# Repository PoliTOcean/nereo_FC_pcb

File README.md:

# nereo_FC_pcb

Flight controller di Nereo (STM32F4, 2 layer).
Firmware: [nereo_FC_firmware](https://github.com/PoliTOcean/nereo_FC_firmware)

| Top | Bottom |
|---|---|
|  |  |

> I file di produzione (gerber, BOM, PDF dello schema) si scaricano dalla scheda **Actions** → ultimo run → **pcb-outputs**.

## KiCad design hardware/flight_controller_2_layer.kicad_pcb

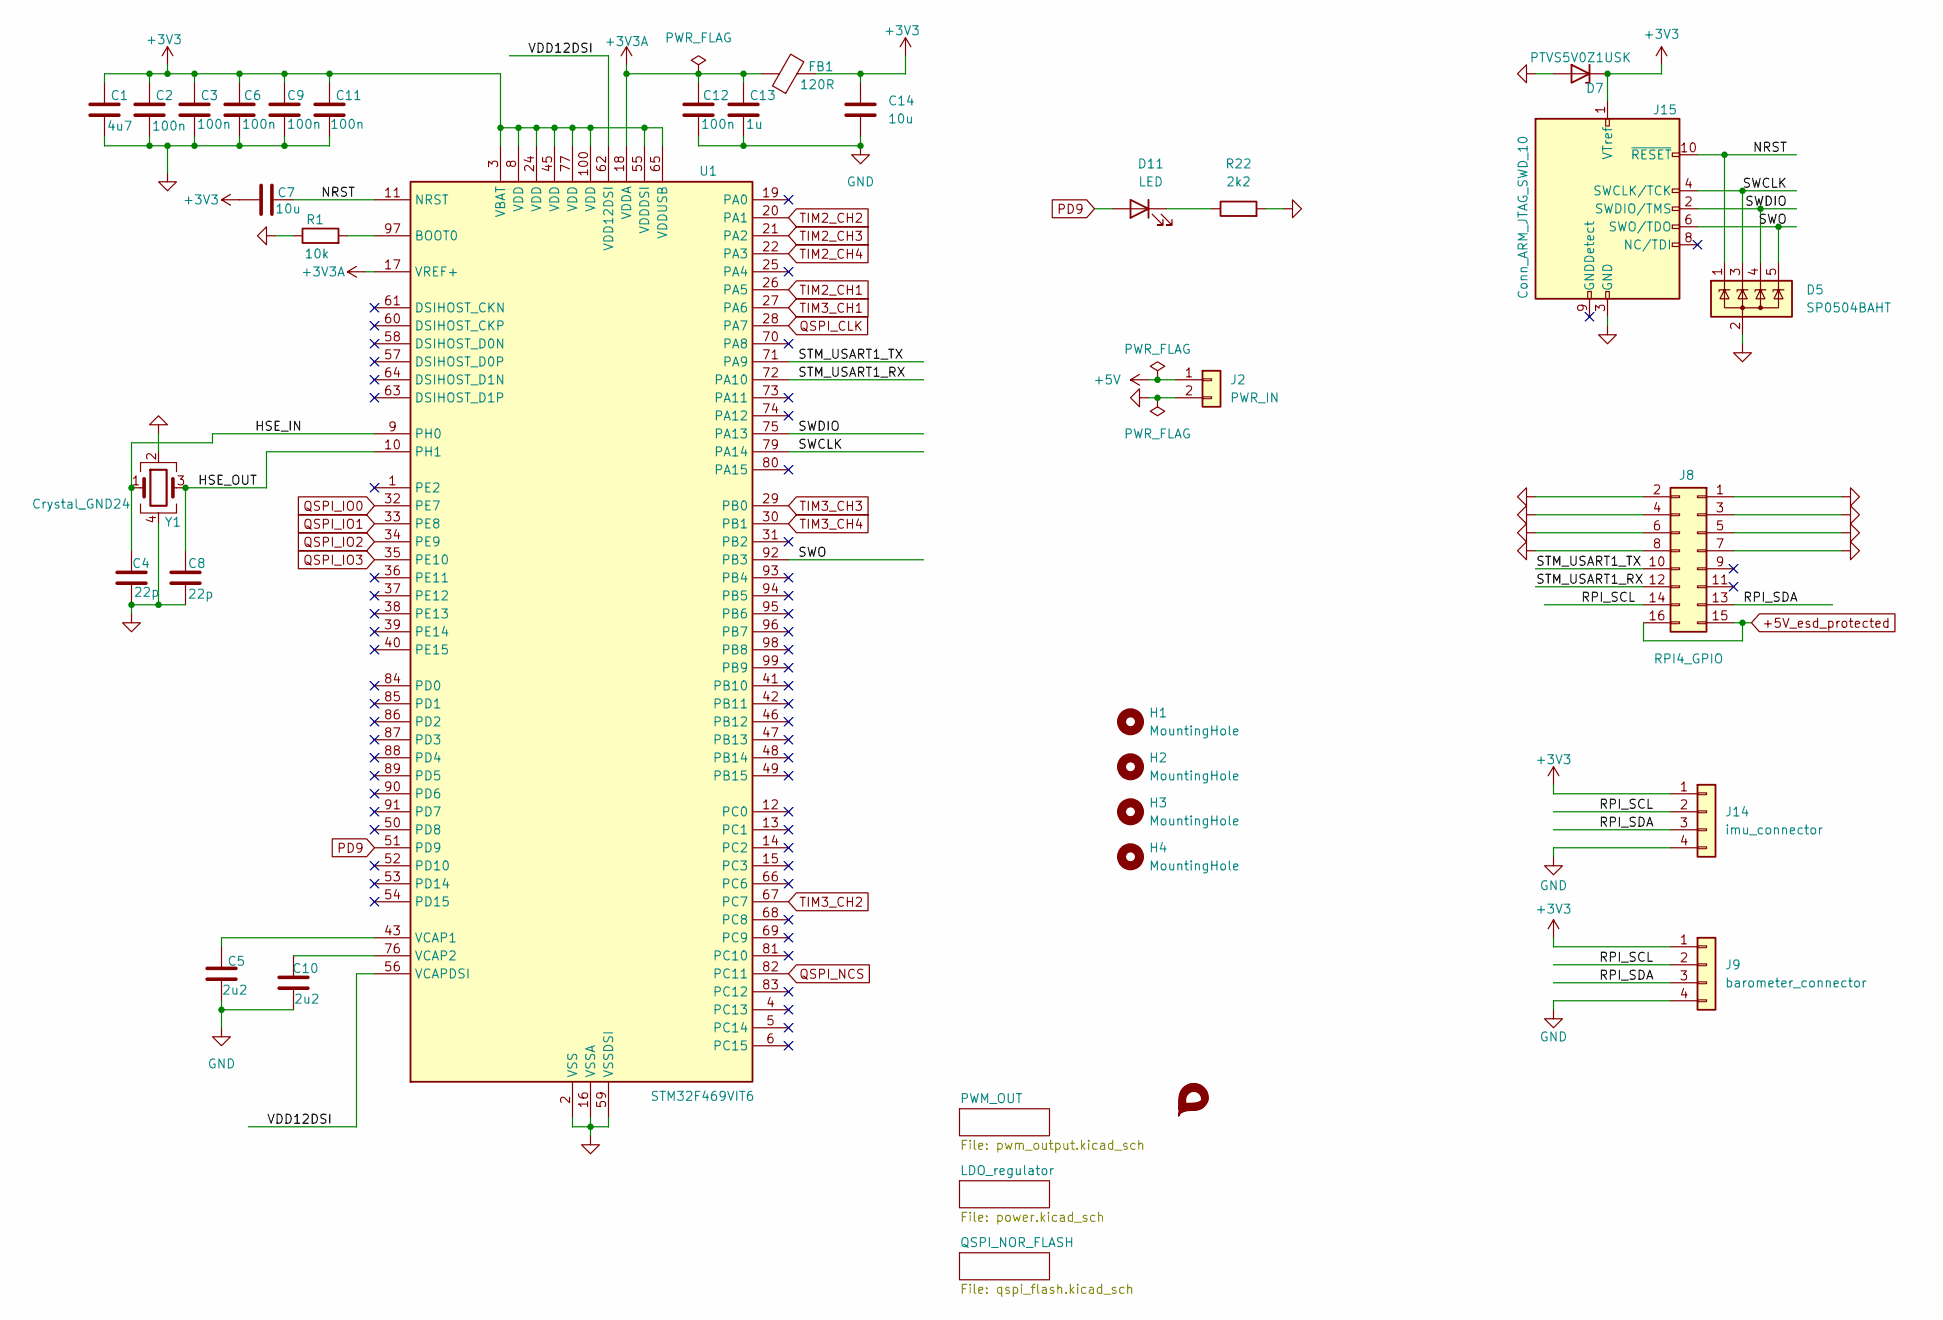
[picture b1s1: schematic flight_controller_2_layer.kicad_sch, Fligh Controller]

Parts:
C1: 4u7; C_0603_1608Metric
C2, C3, C6, C9, C11, C12: 100n; C_0603_1608Metric
C4, C8: 22p; C_0603_1608Metric
C5, C10: 2u2; C_0603_1608Metric
C7, C14: 10u; C_0603_1608Metric
C13: 1u; C_0603_1608Metric
D5: SP0504BAHT; SOT-23-5
D7: PTVS5V0Z1USK; Nexperia_DSN1608-2_1.6x0.8mm
D11: LED; LED_0603_1608Metric
FB1: 120R; L_0603_1608Metric
G1: LOGO; Logo PoliTOcean
H1, H2, H3, H4: MountingHole; MountingHole_2.7mm_M2.5
J2: PWR_IN; JST_VH_B2P-VH_1x02_P3.96mm_Vertical
J8: RPI4_GPIO; IDC-Header_2x08_P2.54mm_Vertical
J9: barometer_connector; JST_XH_B4B-XH-A_1x04_P2.50mm_Vertical
J14: imu_connector; JST_XH_B4B-XH-A_1x04_P2.50mm_Vertical
J15: Conn_ARM_JTAG_SWD_10; PinHeader_2x05_P1.27mm_Vertical_SMD
R1: 10k; R_0603_1608Metric
R22: 2k2; R_0603_1608Metric
U1: STM32F469VIT6; LQFP-100_14x14mm_P0.5mm
Y1: Crystal_GND24; Crystal_SMD_Abracon_ABM3B-4Pin_5.0x3.2mm

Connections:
+3V3: C1.1, C2.1, C3.1, C6.1, C7.1, C9.1, C11.1, C14.1, D7.1 (K), FB1.2, J9.1, J14.1, J15.1 (VTref), U1.3 (VBAT), U1.8 (VDD), U1.24 (VDD), U1.45 (VDD), U1.55 (VDDDSI), U1.65 (VDDUSB), U1.77 (VDD), U1.100 (VDD); also elsewhere on the board
+3V3A: C12.1, C13.1, FB1.1, U1.17 (VREF+), U1.18 (VDDA)
+5V: J2.1; also elsewhere on the board
+5V_esd_protected: J8.15, J8.16; also elsewhere on the board
/HSE_IN: C4.1, U1.9 (PH0), Y1.1
/HSE_OUT: C8.1, U1.10 (PH1), Y1.3
/NRST: C7.2, D5.1 (K), J15.10 (~RESET), U1.11 (NRST)
/RPI_SCL: J8.14, J9.2, J14.2
/RPI_SDA: J8.13, J9.3, J14.3
/STM_USART1_RX: J8.12, U1.72 (PA10)
/STM_USART1_TX: J8.10, U1.71 (PA9)
/SWCLK: D5.3 (K), J15.4 (SWCLK/TCK), U1.79 (PA14)
/SWDIO: D5.4 (K), J15.2 (SWDIO/TMS), U1.75 (PA13)
/SWO: D5.5 (K), J15.6 (SWO/TDO), U1.92 (PB3)
/VDD12DSI: U1.56 (VCAPDSI), U1.62 (VDD12DSI)
GND: C1.2, C2.2, C3.2, C4.2, C5.2, C6.2, C8.2, C9.2, C10.2, C11.2, C12.2, C13.2, C14.2, D5.2 (A), D7.2 (A), J2.2, J8.1, J8.2, J8.3, J8.4, J8.5, J8.6, J8.7, J8.8, J9.4, J14.4, J15.3 (GND), J15.5 (GND), R1.1, R22.2, U1.2 (VSS), U1.7 (VSS), U1.16 (VSSA), U1.23 (VSS), U1.44 (VSS), U1.59 (VSSDSI), U1.78 (VSS), Y1.2, Y1.4; also elsewhere on the board
unnamed: D11.1 (K), R22.1
unnamed: R1.2, U1.97 (BOOT0)
unnamed: C5.1, U1.43 (VCAP1)
unnamed: C10.1, U1.76 (VCAP2)
PD9: D11.2 (A), U1.51 (PD9)
QSPI_CLK: U1.28 (PA7); also elsewhere on the board
QSPI_IO0: U1.32 (PE7); also elsewhere on the board
QSPI_IO1: U1.33 (PE8); also elsewhere on the board
QSPI_IO2: U1.34 (PE9); also elsewhere on the board
QSPI_IO3: U1.35 (PE10); also elsewhere on the board
QSPI_NCS: U1.82 (PC11); also elsewhere on the board
TIM2_CH1: U1.26 (PA5); also elsewhere on the board
TIM2_CH2: U1.20 (PA1); also elsewhere on the board
TIM2_CH3: U1.21 (PA2); also elsewhere on the board
TIM2_CH4: U1.22 (PA3); also elsewhere on the board
TIM3_CH1: U1.27 (PA6); also elsewhere on the board
TIM3_CH2: U1.67 (PC7); also elsewhere on the board
TIM3_CH3: U1.29 (PB0); also elsewhere on the board
TIM3_CH4: U1.30 (PB1); also elsewhere on the board

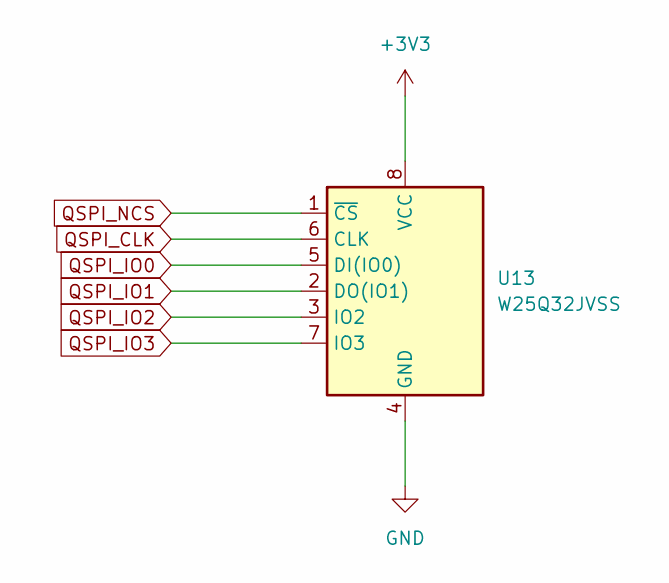
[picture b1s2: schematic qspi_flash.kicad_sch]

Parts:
U13: W25Q32JVSS; SOIC-8_5.23x5.23mm_P1.27mm

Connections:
+3V3: U13.8 (VCC); also elsewhere on the board
GND: U13.4 (GND); also elsewhere on the board
QSPI_CLK: U13.6 (CLK); also elsewhere on the board
QSPI_IO0: U13.5 (DI(IO0)); also elsewhere on the board
QSPI_IO1: U13.2 (DO(IO1)); also elsewhere on the board
QSPI_IO2: U13.3 (IO2); also elsewhere on the board
QSPI_IO3: U13.7 (IO3); also elsewhere on the board
QSPI_NCS: U13.1 (~CS); also elsewhere on the board

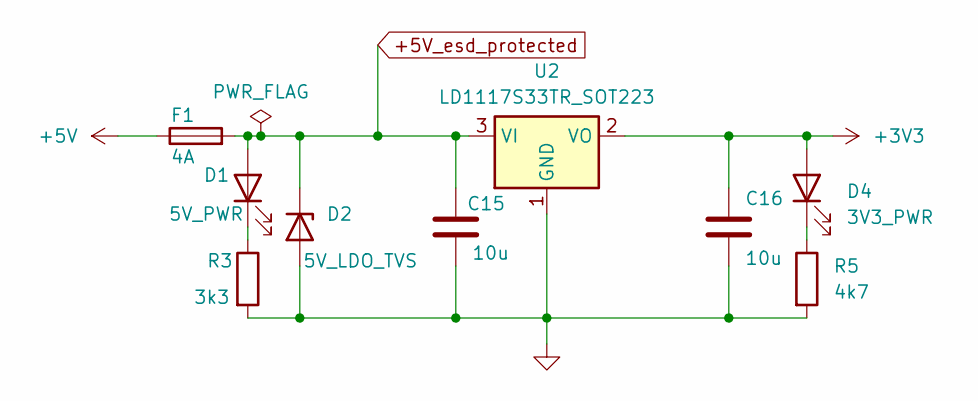
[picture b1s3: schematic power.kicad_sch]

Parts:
C15, C16: 10u; C_0603_1608Metric
D1: 5V_PWR; LED_0603_1608Metric
D2: 5V_LDO_TVS; Nexperia_DSN1608-2_1.6x0.8mm
D4: 3V3_PWR; LED_0603_1608Metric
F1: 4A; Fuseholder_Clip-5x20mm_Littelfuse_111_Lateral_P18.80x5.00mm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
R3: 3k3; R_0603_1608Metric
R5: 4k7; R_0603_1608Metric
U2: LD1117S33TR_SOT223; SOT-223-3_TabPin2

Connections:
+3V3: C16.1, D4.2 (A), U2.2 (VO); also elsewhere on the board
+5V: F1.1; also elsewhere on the board
+5V_esd_protected: C15.1, D1.2 (A), D2.1 (K), F1.2, U2.3 (VI); also elsewhere on the board
GND: C15.2, C16.2, D2.2 (A), R3.2, R5.2, U2.1 (GND); also elsewhere on the board
unnamed: D1.1 (K), R3.1
unnamed: D4.1 (K), R5.1

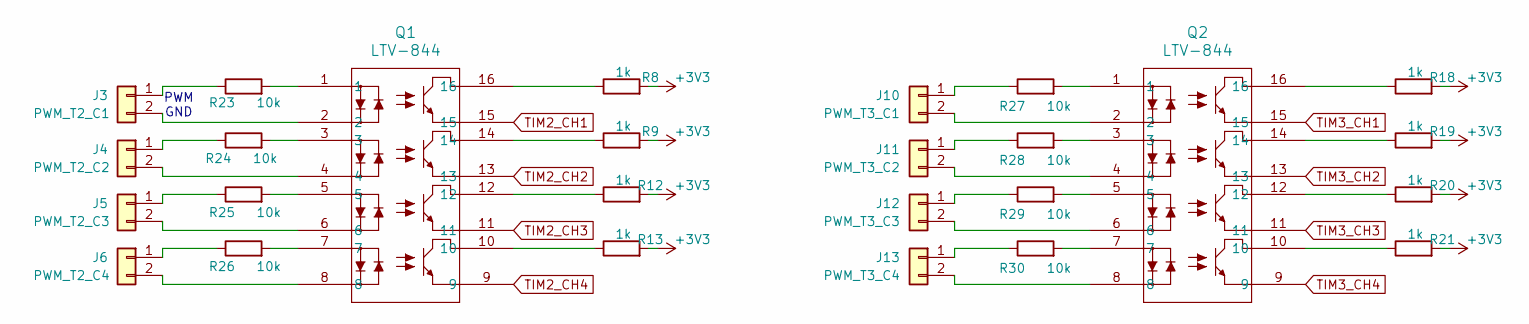
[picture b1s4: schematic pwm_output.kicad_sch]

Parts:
J3: PWM_T2_C1; JST_XH_B2B-XH-A_1x02_P2.50mm_Vertical
J4: PWM_T2_C2; JST_XH_B2B-XH-A_1x02_P2.50mm_Vertical
J5: PWM_T2_C3; JST_XH_B2B-XH-A_1x02_P2.50mm_Vertical
J6: PWM_T2_C4; JST_XH_B2B-XH-A_1x02_P2.50mm_Vertical
J10: PWM_T3_C1; JST_XH_B2B-XH-A_1x02_P2.50mm_Vertical
J11: PWM_T3_C2; JST_XH_B2B-XH-A_1x02_P2.50mm_Vertical
J12: PWM_T3_C3; JST_XH_B2B-XH-A_1x02_P2.50mm_Vertical
J13: PWM_T3_C4; JST_XH_B2B-XH-A_1x02_P2.50mm_Vertical
Q1, Q2: LTV-844; LTV-844_LTO
R8, R9, R12, R13, R18, R19, R20, R21: 1k; R_0603_1608Metric
R23, R24, R25, R26, R27, R28, R29, R30: 10k; R_0603_1608Metric

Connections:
+3V3: R8.2, R9.2, R12.2, R13.2, R18.2, R19.2, R20.2, R21.2; also elsewhere on the board
unnamed: J3.1, R23.1
unnamed: J3.2, Q1.2
unnamed: J4.1, R24.1
unnamed: J4.2, Q1.4
unnamed: J5.1, R25.1
unnamed: J5.2, Q1.6
unnamed: J6.1, R26.1
unnamed: J6.2, Q1.8
unnamed: J10.1, R27.1
unnamed: J10.2, Q2.2
unnamed: J11.1, R28.1
unnamed: J11.2, Q2.4
unnamed: J12.1, R29.1
unnamed: J12.2, Q2.6
unnamed: J13.1, R30.1
unnamed: J13.2, Q2.8
unnamed: Q1.1, R23.2
unnamed: Q1.3, R24.2
unnamed: Q1.5, R25.2
unnamed: Q1.7, R26.2
unnamed: Q1.10, R13.1
unnamed: Q1.12, R12.1
unnamed: Q1.14, R9.1
unnamed: Q1.16, R8.1
unnamed: Q2.1, R27.2
unnamed: Q2.3, R28.2
unnamed: Q2.5, R29.2
unnamed: Q2.7, R30.2
unnamed: Q2.10, R21.1
unnamed: Q2.12, R20.1
unnamed: Q2.14, R19.1
unnamed: Q2.16, R18.1
TIM2_CH1: Q1.15; also elsewhere on the board
TIM2_CH2: Q1.13; also elsewhere on the board
TIM2_CH3: Q1.11; also elsewhere on the board
TIM2_CH4: Q1.9; also elsewhere on the board
TIM3_CH1: Q2.15; also elsewhere on the board
TIM3_CH2: Q2.13; also elsewhere on the board
TIM3_CH3: Q2.11; also elsewhere on the board
TIM3_CH4: Q2.9; also elsewhere on the board

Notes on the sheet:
PWM GND

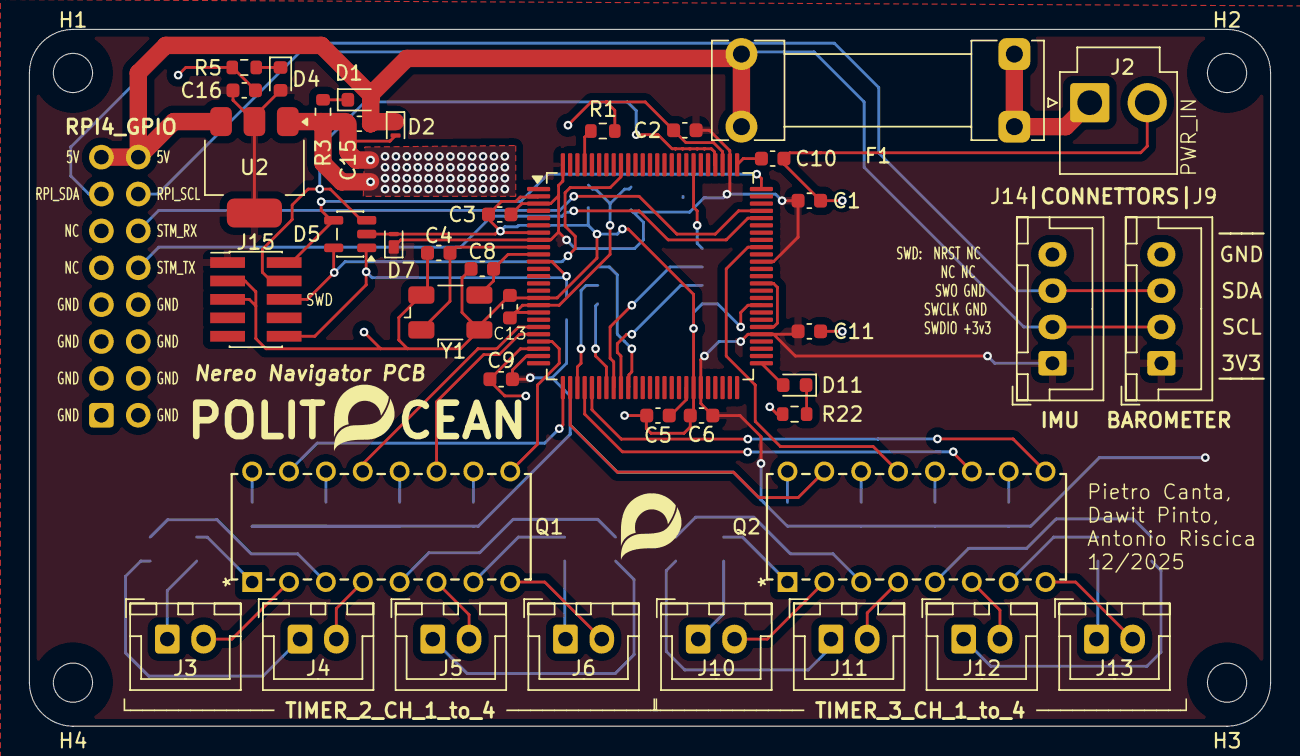
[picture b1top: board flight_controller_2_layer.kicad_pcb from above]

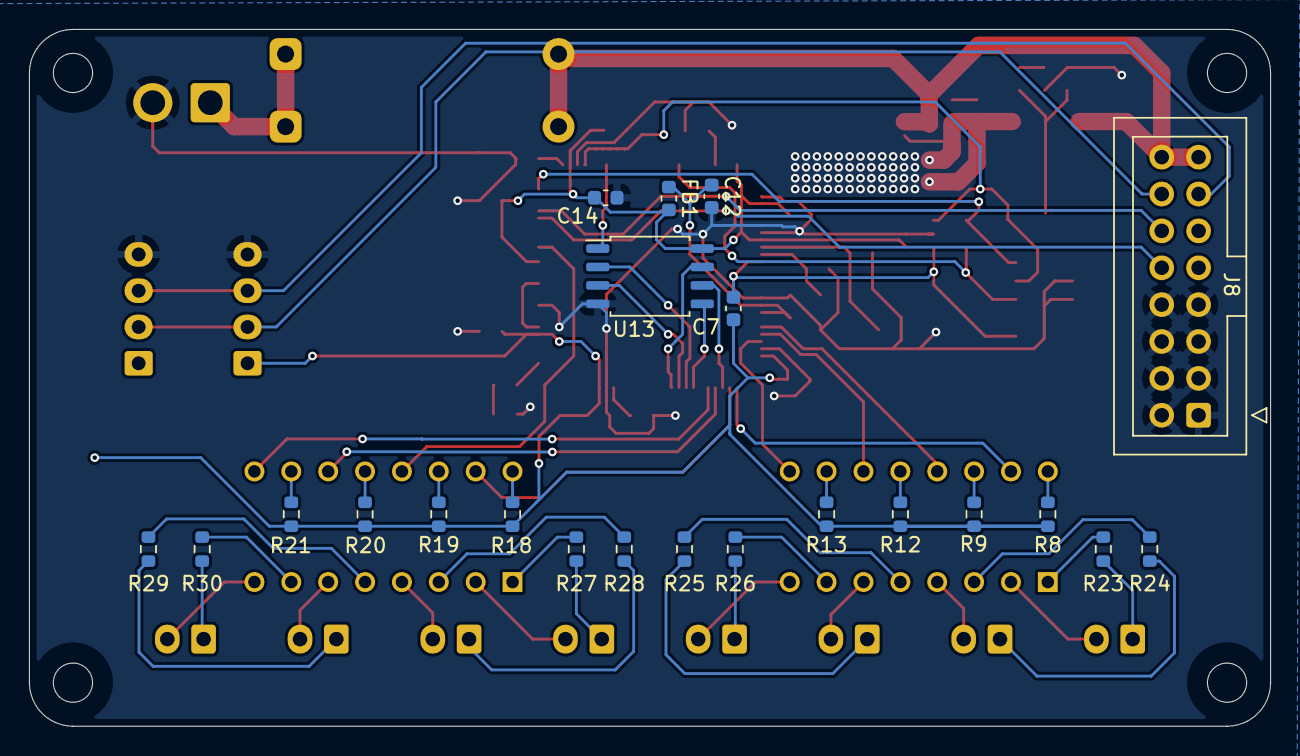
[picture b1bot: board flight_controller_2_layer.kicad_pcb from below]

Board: 2 copper layers, 85.5 x 48.0 mm, 67 parts (22 on the bottom side), 69 nets.
